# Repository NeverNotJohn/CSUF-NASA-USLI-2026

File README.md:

# California State University, Fresno NASA USLI 
California State University, Fresno (CSUF) GitHub for the 2025-2026 NASA USLI Competition 

## File Structure
### Hardware
Schematics, PCB, KiCad project, etc.
### Software
Code made in C/C++ using FreeRTOS and Arduino. Development using the PlatformIO IDE

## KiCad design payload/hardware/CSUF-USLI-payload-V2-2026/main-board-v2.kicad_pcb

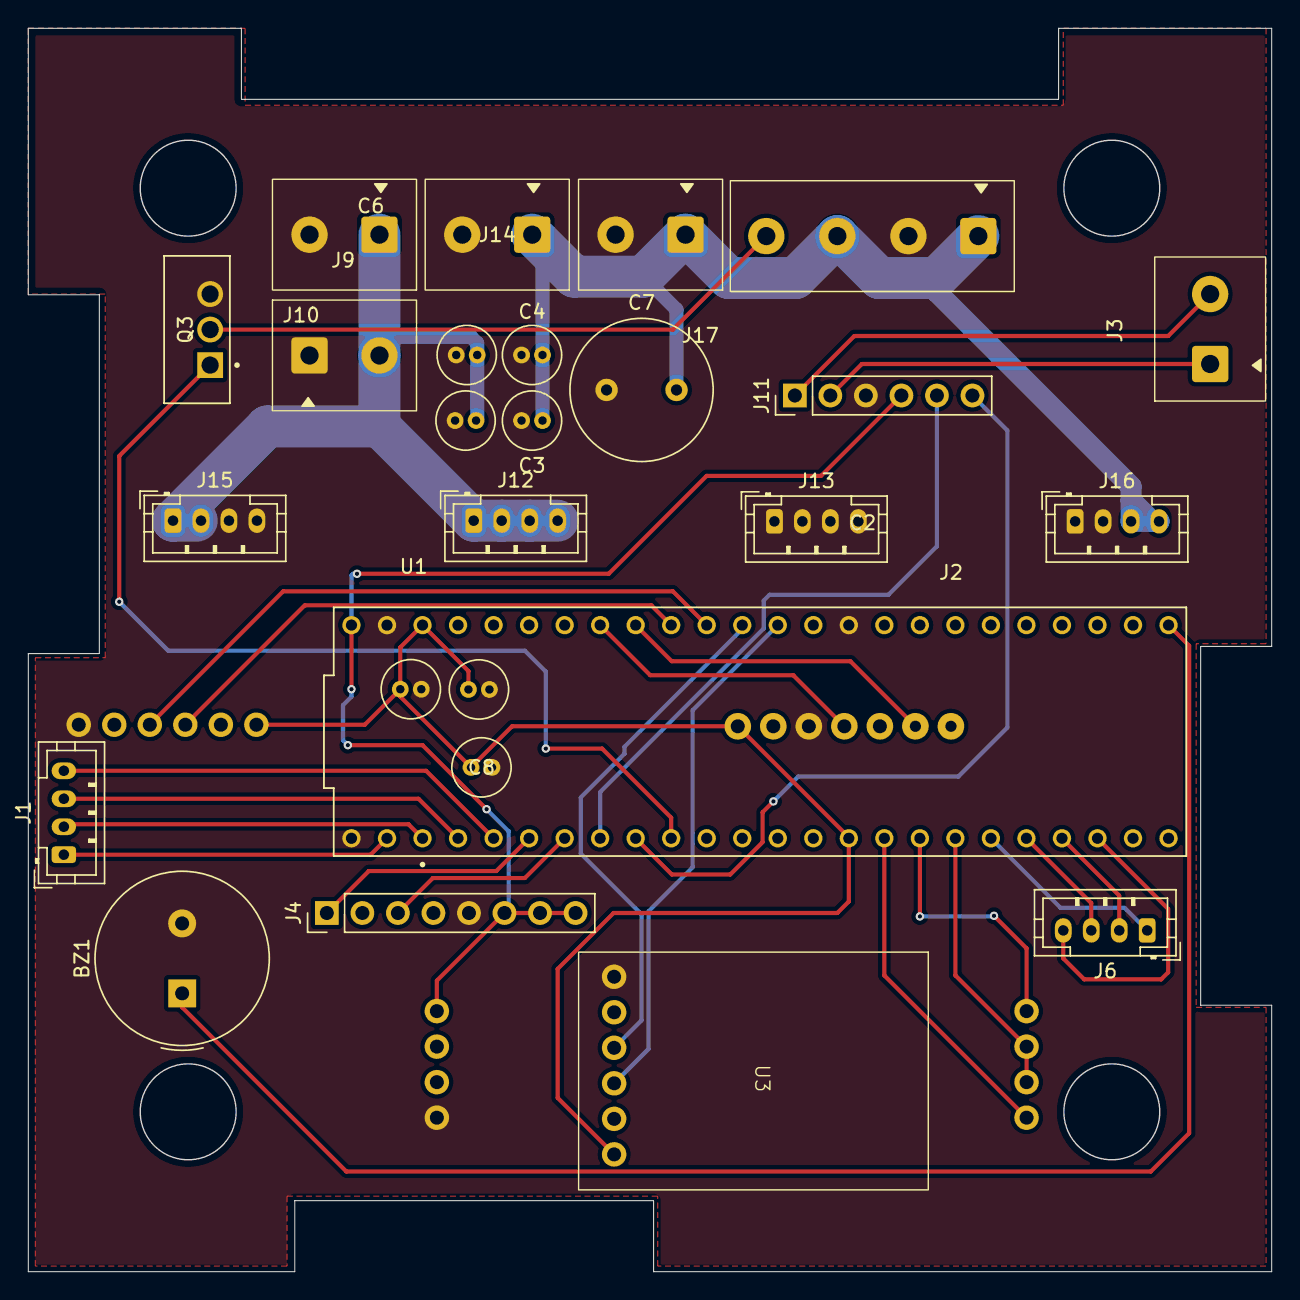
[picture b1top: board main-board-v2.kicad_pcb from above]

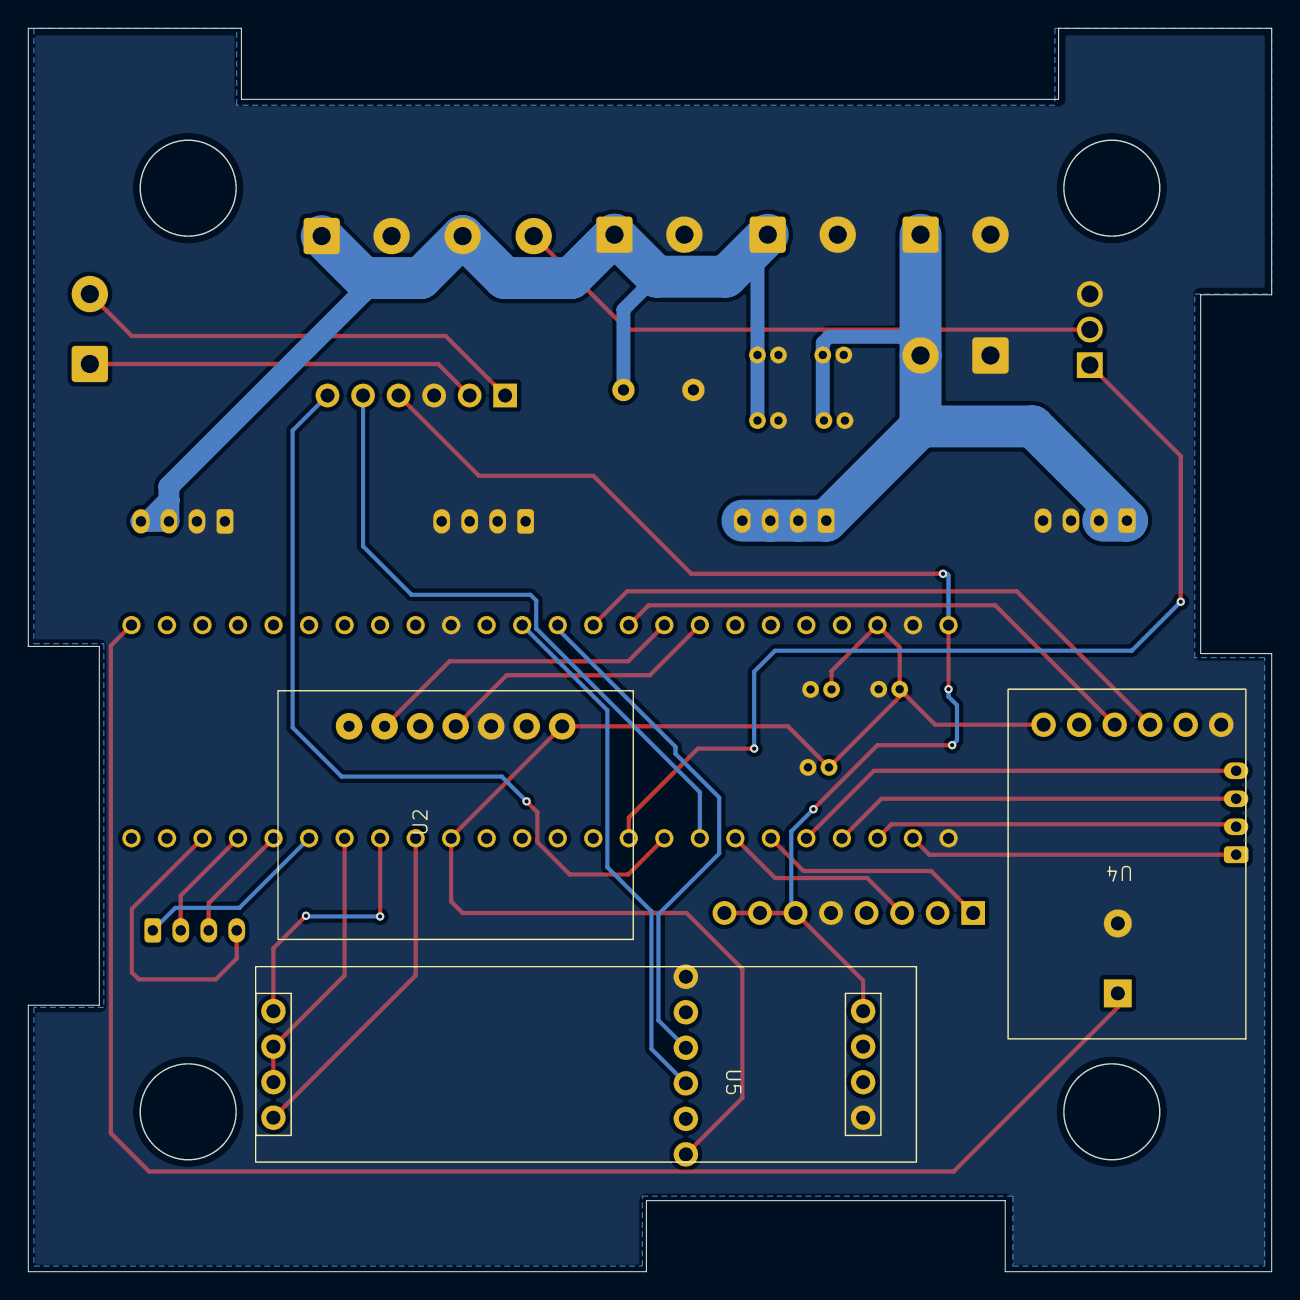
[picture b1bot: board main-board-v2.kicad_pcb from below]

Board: 2 copper layers, 88.9 x 88.9 mm, 29 parts (3 on the bottom side), 31 nets.

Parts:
BZ1: Buzzer; Buzzer_TDK_PS1240P02BT_D12.2mm_H6.5mm
C1, C2, C3, C5, C8: 0.1 uF; C_Radial_D4.0mm_H7.0mm_P1.50mm
C4, C6: 1 uF; C_Radial_D4.0mm_H7.0mm_P1.50mm
C7: 330 uF; C_Radial_D10.0mm_H12.5mm_P5.00mm
J1: Servo JST; JST_PH_B4B-PH-K_1x04_P2.00mm_Vertical
J2: Drill x 11.1V OUT; Edit_TerminalBlock_Phoenix_MKDS-1,5-2_1x04_P5.00mm_Horizont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
J3: Motor Power; Edit_TerminalBlock_Phoenix_MKDS-1,5-2_1x02_P5.00mm_Horizont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
J4: BTS7960 Output; PinHeader_1x08_P2.54mm_Vertical
J6: Reserve JST; JST_PH_B4B-PH-K_1x04_P2.00mm_Vertical
J9: Soil Sensor Power; Edit_TerminalBlock_Phoenix_MKDS-1,5-2_1x02_P5.00mm_Horizont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
J10: 8.4V IN; Edit_TerminalBlock_Phoenix_MKDS-1,5-2_1x02_P5.00mm_Horizont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
J11: Chassis Input; PinHeader_1x06_P2.54mm_Vertical
J12: Servo VCC; JST_PH_B4B-PH-K_1x04_P2.00mm_Vertical
J13: Servo GND; JST_PH_B4B-PH-K_1x04_P2.00mm_Vertical
J14: 11.1V IN; Edit_TerminalBlock_Phoenix_MKDS-1,5-2_1x02_P5.00mm_Horizont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
J15: 8.4V RESERVE; JST_PH_B4B-PH-K_1x04_P2.00mm_Vertical
J16: 11.1V RESERVE; JST_PH_B4B-PH-K_1x04_P2.00mm_Vertical
J17: Driver Input; Edit_TerminalBlock_Phoenix_MKDS-1,5-2_1x02_P5.00mm_Horizont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
Q3: IRLZ44N
U1: DEV-16771; MODULE_DEV-16771
U2: Adafruit BMP280; BMP280
U3, U4: RYLR896; REYAX RYLR896
U5: Modbus to UART; Modbus_to_UART

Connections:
+3V3: C1.1, C2.1, C8.1, U1.3.3V_1 (3.3V), U1.3.3V_2 (3.3V), U2.1 (Vin), U3.1 (VDD), U4.1 (VDD)
+5V: J4.6, J4.7, J4.8, J11.4, U1.VIN, U5.5 (VCC)
+8.4V: C5.2, C6.2, J9.2, J10.1, J12.1, J12.2, J12.3, J12.4, J15.1, J15.2
+11.1V: C3.2, C4.2, C7.2, J2.1, J2.3, J14.1, J16.3, J16.4, J17.1
Chassis_Encoder_A: J11.5, U1.6 (OUT1D)
Chassis_Encoder_B: J11.6, U1.7 (RX2)
DRILL: Q3.1 (G), U1.8 (TX2)
GND: BZ1.2 (-), C1.2, C2.2, C3.1, C4.1, C5.1, C6.1, C7.1, C8.2, J2.2, J4.5, J9.1, J10.2, J11.3, J13.1, J13.2, J13.3, J13.4, J14.2, J15.3, J15.4, J16.1, J16.2, J17.2, Q3.3 (S), U1.GND1 (GND), U1.GND2 (GND), U1.GND3 (GND), U2.3 (GND), U3.6 (GND), U4.6 (GND), U5.8 (GND)
LPWM: J4.3, U1.5 (IN2)
unnamed: BZ1.1 (+), U1.33 (MCLK2)
unnamed: J2.4, Q3.2 (D)
unnamed: J3.2, J11.1
unnamed: J3.1, J11.2
RESERVE_0: J6.1, U1.27 (A13)
RESERVE_1: J6.2, U1.29 (TX7)
RESERVE_2: J6.3, U1.28 (RX7)
RESERVE_3: J6.4, U1.30 (CRX3)
RPWM: J4.1, U1.4 (BCLK2)
RX3: U1.15 (A1), U3.4 (TXD)
RX4: U1.16 (A2), U4.4 (TXD)
RX6: U1.25 (A11), U5.4 (RO)
SCL: U1.19 (A5), U2.4 (SCK)
SDA: U1.18 (A4), U2.6 (SDI)
SERVO_0: J1.1, U1.0 (RX1)
SERVO_1: J1.2, U1.1 (TX1)
SERVO_2: J1.3, U1.2 (OUT2)
SERVO_3: J1.4, U1.3 (LRCLK2)
SOIL_ENABLE: U1.26 (A12), U5.2 (DE), U5.3 (RE)
TX3: U1.14 (A0), U3.3 (RXD)
TX4: U1.17 (A3), U4.3 (RXD)
TX6: U1.24 (A10), U5.1 (DI)

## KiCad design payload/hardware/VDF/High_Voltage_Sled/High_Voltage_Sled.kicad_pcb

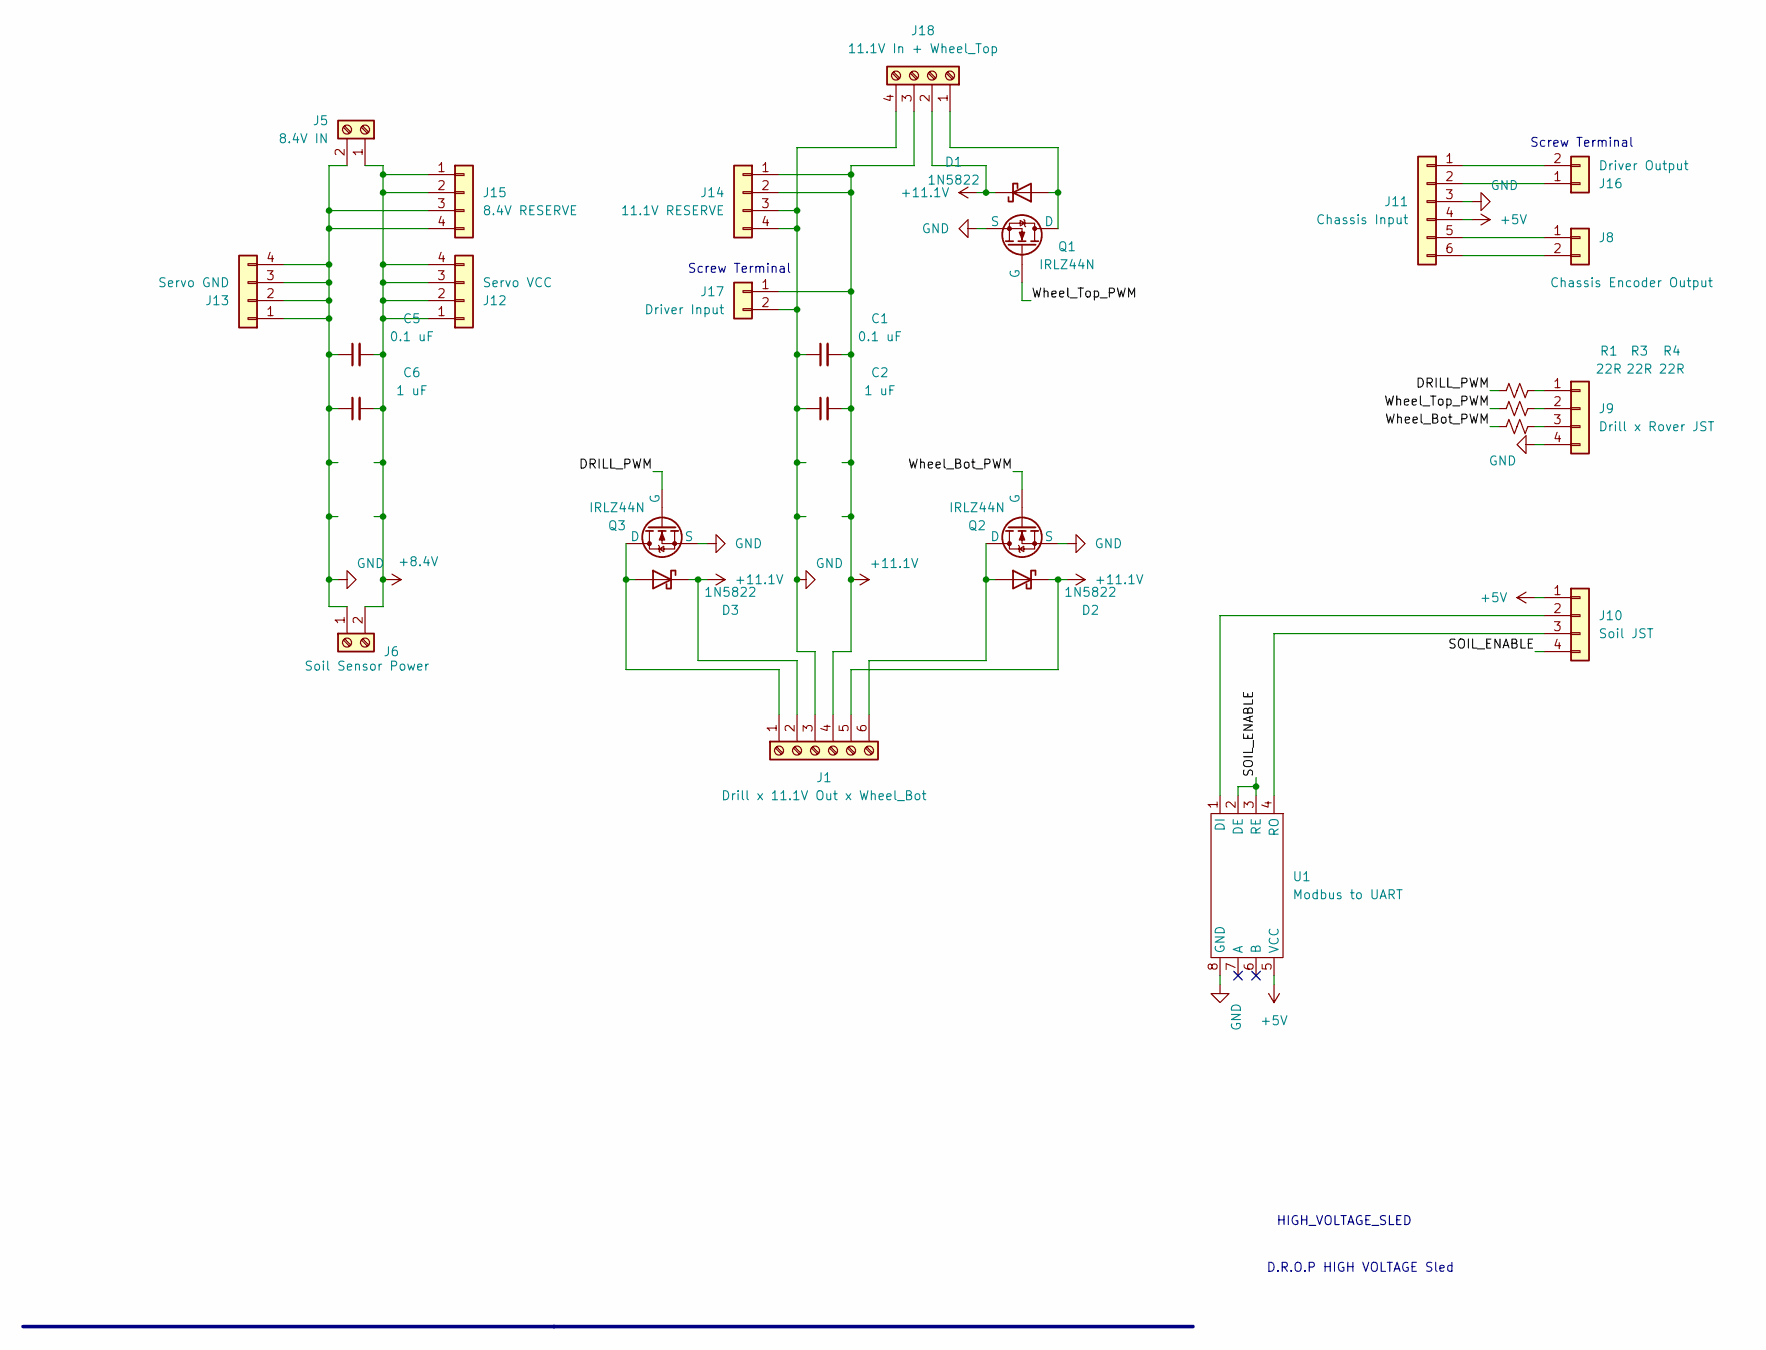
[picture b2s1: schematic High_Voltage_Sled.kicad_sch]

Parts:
C1, C5: 0.1 uF; C_Radial_D4.0mm_H7.0mm_P1.50mm
C2, C6: 1 uF; C_Radial_D4.0mm_H7.0mm_P1.50mm
D1, D2, D3: 1N5822; D_DO-201AD_P15.24mm_Horizontal
J1: Drill x 11.1V Out x Wheel_Bot; Edit_TerminalBlock_Phoenix_MKDS-1,5-2_1x06_P5.00mm_Horizont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
J5: 8.4V IN; Edit_TerminalBlock_Phoenix_MKDS-1,5-2_1x02_P5.00mm_Horizont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
J6: Soil Sensor Power; Edit_TerminalBlock_Phoenix_MKDS-1,5-2_1x02_P5.00mm_Horizont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
J8: Chassis Encoder Output; JST_PH_B2B-PH-K_1x02_P2.00mm_Vertical
J9: Drill x Rover JST; JST_PH_B4B-PH-K_1x04_P2.00mm_Vertical
J10: Soil JST; JST_PH_B4B-PH-K_1x04_P2.00mm_Vertical
J11: Chassis Input; PinHeader_1x06_P2.54mm_Vertical
J12: Servo VCC; JST_PH_B4B-PH-K_1x04_P2.00mm_Vertical
J13: Servo GND; JST_PH_B4B-PH-K_1x04_P2.00mm_Vertical
J14: 11.1V RESERVE; JST_PH_B4B-PH-K_1x04_P2.00mm_Vertical
J15: 8.4V RESERVE; JST_PH_B4B-PH-K_1x04_P2.00mm_Vertical
J16: Driver Output; Edit_TerminalBlock_Phoenix_MKDS-1,5-2_1x02_P5.00mm_Horizont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
J17: Driver Input; Edit_TerminalBlock_Phoenix_MKDS-1,5-2_1x02_P5.00mm_Horizont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
J18: 11.1V In + Wheel_Top; Edit_TerminalBlock_Phoenix_MKDS-1,5-2_1x04_P5.00mm_Horizont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
Q1, Q2, Q3: IRLZ44N
R1, R3, R4: 22R; R_Axial_DIN0207_L6.3mm_D2.5mm_P2.54mm_Vertical
U1: Modbus to UART; Modbus_to_UART

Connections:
+5V: J10.1, J11.4, U1.5 (VCC)
+8.4V: C5.2, C6.2, J5.1, J6.2, J12.1, J12.2, J12.3, J12.4, J15.1, J15.2
+11.1V: C1.2, C2.2, D1.1 (K), D2.1 (K), D3.1 (K), J1.2, J1.4, J1.5, J14.1, J14.2, J17.1, J18.2, J18.3
/DRILL_PWM: Q3.1 (G), R4.1
/SOIL_ENABLE: J10.4, U1.2 (DE), U1.3 (RE)
/Wheel_Bot_PWM: Q2.1 (G), R3.1
/Wheel_Top_PWM: Q1.1 (G), R1.1
GND: C1.1, C2.1, C5.1, C6.1, J1.3, J5.2, J6.1, J9.4, J11.3, J13.1, J13.2, J13.3, J13.4, J14.3, J14.4, J15.3, J15.4, J17.2, J18.4, Q1.3 (S), Q2.3 (S), Q3.3 (S), U1.8 (GND)
unnamed: D1.2 (A), J18.1, Q1.2 (D)
unnamed: D2.2 (A), J1.6, Q2.2 (D)
unnamed: D3.2 (A), J1.1, Q3.2 (D)
unnamed: J9.1, R4.2
unnamed: J9.2, R1.2
unnamed: J9.3, R3.2
unnamed: J10.2, U1.1 (DI)
unnamed: J10.3, U1.4 (RO)
unnamed: J11.1, J16.2
unnamed: J11.2, J16.1
unnamed: J8.1, J11.5
unnamed: J8.2, J11.6

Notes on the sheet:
Screw Terminal
HIGH_VOLTAGE_SLED
D.R.O.P HIGH VOLTAGE Sled

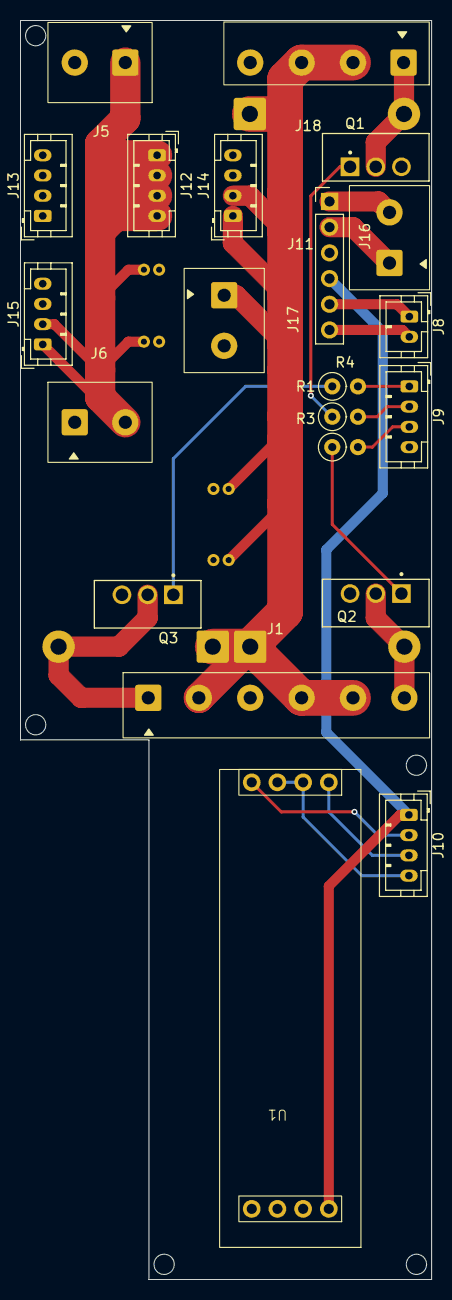
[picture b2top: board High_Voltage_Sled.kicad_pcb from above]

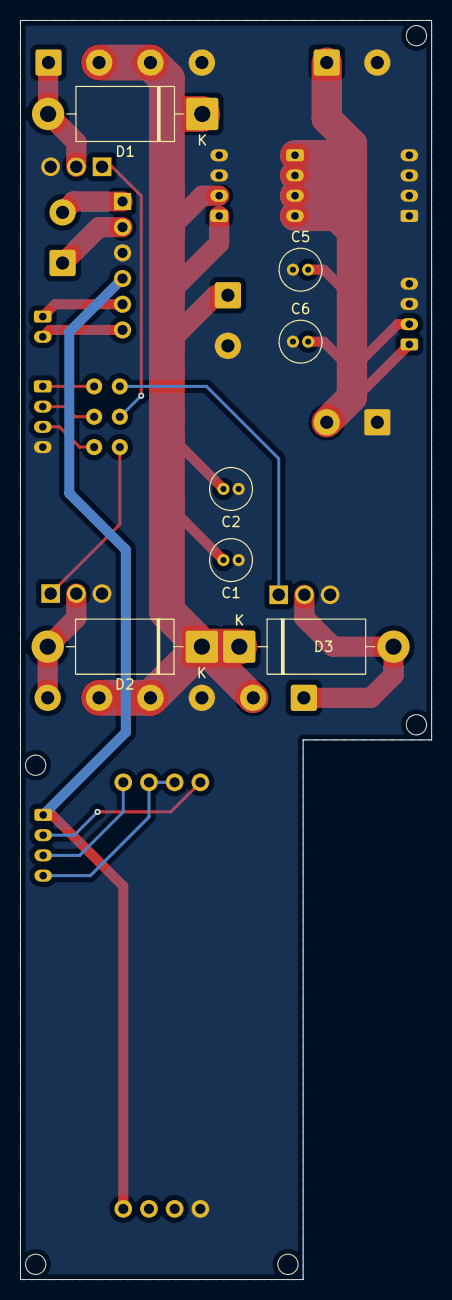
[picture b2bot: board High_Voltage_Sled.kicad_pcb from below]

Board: 2 copper layers, 40.6 x 124.5 mm, 28 parts (7 on the bottom side), 20 nets.

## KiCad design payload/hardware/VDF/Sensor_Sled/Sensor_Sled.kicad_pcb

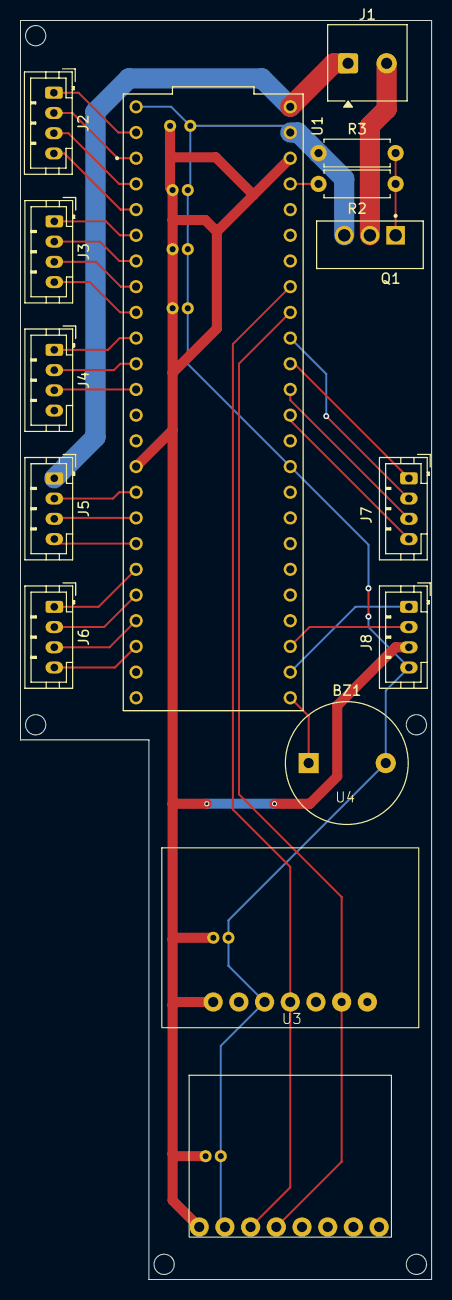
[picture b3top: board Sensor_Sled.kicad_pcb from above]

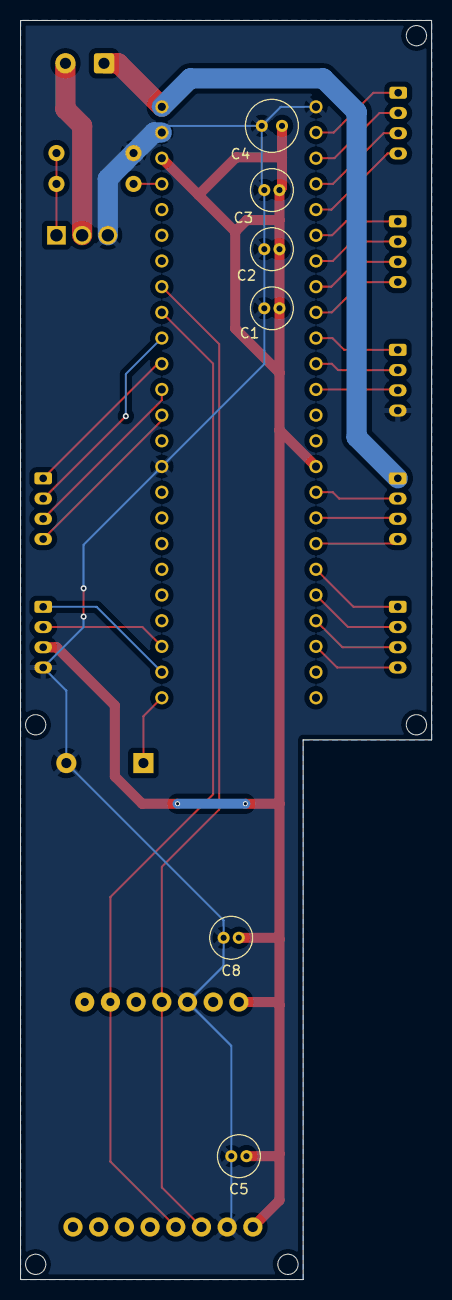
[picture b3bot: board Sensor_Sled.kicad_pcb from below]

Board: 2 copper layers, 40.6 x 124.5 mm, 21 parts (6 on the bottom side), 33 nets.

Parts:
BZ1: Buzzer; Buzzer_TDK_PS1240P02BT_D12.2mm_H6.5mm
C1, C5, C8: 0.1 uF; C_Radial_D4.0mm_H7.0mm_P1.50mm
C2: 1 uF; C_Radial_D4.0mm_H7.0mm_P1.50mm
C3: 10 uF; C_Radial_D4.0mm_H7.0mm_P1.50mm
C4: 100 uF; C_Radial_D5.0mm_H7.0mm_P2.00mm
J1: TD3 Connection; TerminalBlock_Phoenix_MKDS-1-2-3.81_1x02_P3.81mm_Horizontal
J2: Servo JST; JST_PH_B4B-PH-K_1x04_P2.00mm_Vertical
J3: Chassis JST; JST_PH_B4B-PH-K_1x04_P2.00mm_Vertical
J4: Drill x Rover JST; JST_PH_B4B-PH-K_1x04_P2.00mm_Vertical
J5: Soil JST; JST_PH_B4B-PH-K_1x04_P2.00mm_Vertical
J6: Reserve JST; JST_PH_B4B-PH-K_1x04_P2.00mm_Vertical
J7: RYLR896 JST; JST_PH_B4B-PH-K_1x04_P2.00mm_Vertical
J8: GPS x Power JST; JST_PH_B4B-PH-K_1x04_P2.00mm_Vertical
Q1: IRLZ44N
R2: 330; R_Axial_DIN0207_L6.3mm_D2.5mm_P7.62mm_Horizontal
R3: 10k; R_Axial_DIN0207_L6.3mm_D2.5mm_P7.62mm_Horizontal
U1: DEV-16771; MODULE_DEV-16771
U3: MPU6050
U4: Adafruit BMP280; BMP280

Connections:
+3V3: C1.1, C2.1, C3.1, C4.1, C5.1, C8.1, J8.3, U1.3.3V_1 (3.3V), U1.3.3V_2 (3.3V), U3.1 (VCC), U4.1 (Vin)
+5V: J1.1, J5.1, U1.VIN
/Chassis_Encoder_A: J3.3, U1.6 (OUT1D)
/Chassis_Encoder_B: J3.4, U1.7 (RX2)
/Chassis_Out_0: J3.1, U1.4 (BCLK2)
/Chassis_Out_1: J3.2, U1.5 (IN2)
/DRILL: J4.1, U1.8 (TX2)
/RESERVE_0: J6.1, U1.27 (A13)
/RESERVE_1: J6.2, U1.28 (RX7)
/RESERVE_2: J6.3, U1.29 (TX7)
/RESERVE_3: J6.4, U1.30 (CRX3)
/ROVER_BOT: J4.3, U1.10 (CS1)
/ROVER_TOP: J4.2, U1.9 (OUT1C)
/RX3: J7.3, U1.15 (A1)
/RX4: J7.1, U1.16 (A2)
/RX6: J5.3, U1.25 (A11)
/RX8: J8.1, U1.34 (RX8)
/SERVO_0: J2.1, U1.0 (RX1)
/SERVO_1: J2.2, U1.1 (TX1)
/SERVO_2: J2.3, U1.2 (OUT2)
/SERVO_3: J2.4, U1.3 (LRCLK2)
/SOIL_ENABLE: J5.4, U1.26 (A12)
/TX3: J7.4, U1.14 (A0)
/TX4: J7.2, U1.17 (A3)
/TX6: J5.2, U1.24 (A10)
/TX8: J8.2, U1.35 (TX8)
GND: BZ1.2 (-), C1.2, C2.2, C3.2, C4.2, C5.2, C8.2, J4.4, J8.4, Q1.3 (S), R3.1, U1.GND1 (GND), U1.GND2 (GND), U1.GND3 (GND), U3.2 (GND), U4.3 (GND)
unnamed: BZ1.1 (+), U1.33 (MCLK2)
unnamed: J1.2, Q1.2 (D)
unnamed: Q1.1 (G), R2.2, R3.2
unnamed: U1.18 (A4), U3.4 (SDA), U4.6 (SDI)
unnamed: U1.19 (A5), U3.3 (SCL), U4.4 (SCK)
unnamed: R2.1, U1.23 (A9)

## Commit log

2025-09-25 Creating Readme
2025-09-25 Created PlatformIO project
2025-09-25 Creating Tempalte for Code - This is BEFORE FreeRTOS
2025-09-26 Made changes to FreeRTOS
2025-09-26 Added KiCad
2025-09-30 some changes
2025-09-30 changed main naming scheme
2025-10-01 Made updates to the file structure
2025-10-03 updated file structure
2025-10-14 changed git ignore to ignore KiCad stuff
2025-10-14 changed naming convention
2025-10-14 Merging Init PCB changes
2025-10-15 made some changes
2025-10-15 asdAdded changes n stuff
2025-10-16 ejfioahsfaspkaspdk
2025-10-17 Motor Diagram Concept
2025-10-18 Added decoupling capacitors
2025-10-20 added BMP280
2025-10-20 BMP280 and LoRa RYLR896 symbols
2025-10-20 Added the final soil sensors
2025-10-27 idk what change i did
2025-10-27 Added ground station schematic
2025-10-29 Rover Subsystem
    Created "generic" symbol library to hold generic symbols (including the 12v drill created earlier)
2025-11-01 Revert "Merge pull request #4 from NeverNotJohn/PDR_Schematic"
    This reverts commit b304c00c3a6b217adf7fd74d4069b9ba7e955c17, reversing
    changes made to a2006b1930044f0c3205c7475f893156ef9e6752.
2025-11-02 KiCad does not like merge requests
2025-11-07 BMP280 Library
    Added in getters for pressure, temp, relative altitude. Also created a calibrating function.
2025-11-07 Changed to doubles
    "double calculateBaselinePressure()"
    "dobule getPressure()"
2025-11-07 MPU6050 Init Library
    connects via I2C on pins 17+18 at address 0x68 or 0x69 (AD0 pin pulled high).
2025-11-07 Don't merge this
    can compile because of issues with defines header file
2025-11-07 Read gyro and accel
    Implementation of "getAcceleration()" and "getAngularAcceleration"
    Vector3D struct is defined in the "MPU6050.h" header file
2025-11-09 Calculate orientation
    "getAngularAcceleration()" to "getAngularVelocity()" (I am an idiot)
    proof of concept "orientationLoop()"
    Drifts very fast, prints to the serial monitor in degrees not very accurate.
2025-11-09 complementary filter
    updated "orientationCalculation()".
    - mutates a vec3 in place.
    - complementary filter with accelerometer data
2025-11-09 unused libs
2025-11-09 BMP280 Library (#5)
    * BMP280 Library
    Added in getters for pressure, temp, relative altitude. Also created a calibrating function.
    * Changed to doubles
    "double calculateBaselinePressure()"
    "dobule getPressure()"
    * Update bmp280.h
2025-11-09 MPU6050 Init Library (#6)
    * MPU6050 Init Library
    connects via I2C on pins 17+18 at address 0x68 or 0x69 (AD0 pin pulled high).
    * Don't merge this
    can compile because of issues with defines header file
    * Read gyro and accel
    Implementation of "getAcceleration()" and "getAngularAcceleration"
2025-11-09 Fixed function output types
2025-11-09 MadgwickAHRS
    Usage of a Madgwick filter for orientation
2025-11-09 merge conflicts
    insane amount of merge conflicts
2025-11-09 output type
2025-11-09 semaphore mutex, madgwick
    can read both the mpu6050 and bmp280 at the "same " time.
    also implements the Madgwick filter for the mpu6050
2025-11-13 First Draft of Schematic
2025-11-14 Refactored main to do my bidding
2025-11-14 Created beep task for funzies
2025-11-14 Create RYLR cpp and header
2025-11-14 Added comments
2025-11-14 Added Some comments
2025-11-14 Added ANNOY_CYAN Flag
2025-11-14 Fixed Some Spacing
2025-11-14 RYLR896 Won't accept inputs
2025-11-14 Time is working now i think lol
2025-11-14 im in pain
2025-11-14 init commit
2025-11-19 wow thats a lot of storage
2025-11-19 hmm changing my idea
2025-11-19 cleaned up lib and preparing for FreeRTOS stuff
2025-11-19 Created I2C header and yeeted to others
2025-11-19 Created I2C header and yeeted to others (#8)
2025-11-19 cleaned code up and increased bmp accuracy
2025-11-20 NEO6M Intergration
    added
    functions to init and get values using the tinygpsplus library
2025-11-25 changed serial port
2025-11-25 Fixed Mutex Glitches
2025-11-25 Bmp280 library (#9)
    * BMP280 Library
    Added in getters for pressure, temp, relative altitude. Also created a calibrating function.
    * Changed to doubles
    "double calculateBaselinePressure()"
    "dobule getPressure()"
    * Update bmp280.h
2025-11-25 cleanup n stuff
2025-11-25 Made changes to debug
2025-11-25 Usage of semaphore and a mutex to read sensors without conflict. Implementation of Madgwick filter. (#7)
    * semaphore mutex, madgwick
    can read both the mpu6050 and bmp280 at the "same " time.
    also implements the Madgwick filter for the mpu6050
    * Update main.cpp
    * Refactored main to do my bidding
    * s
2025-11-26 Created Main task and added buzzer mutex
2025-12-01 changed flight counters
2025-12-02 yay it works
2025-12-02 Single Squashed commit
2025-12-02 MOved time cause i fcked up the merge
2025-12-04 yata
2025-12-05 changed LED output pin
2025-12-07 ignore main.cpp
2025-12-07 SD Card (#12)
    * ignore main.cpp
    * init commit
2025-12-07 Main task (#13)
    * semaphore mutex, madgwick
    can read both the mpu6050 and bmp280 at the "same " time.
    also implements the Madgwick filter for the mpu6050
    * Update main.cpp
    * NEO6M Intergration
    added
2025-12-07 Fixed Pull Request
2025-12-07 Added Mutex for coolio stuff
2025-12-07 Rylr896 (#14)
    * Create RYLR cpp and header
    * Added comments
    * Added Some comments
    * Added ANNOY_CYAN Flag
    * Fixed Some Spacing
    * RYLR896 Won't accept inputs
2025-12-08 mysterious bug has arisen!
2025-12-23 finished base logger
2025-12-23 Logger (#15)
    * mysterious bug has arisen!
    * finished base logger
2025-12-26 i dont even wanna begin to explain
2025-12-26 ground station receives yay
2025-12-26 finished ground station integration
2025-12-26 finished ground station
2025-12-26 Ground comms (#16)
    * i dont even wanna begin to explain
    * ground station receives yay
    * finished ground station integration
    * finished ground station
2025-12-27 subscale ready!
2025-12-27 sd card init
2025-12-27 Fixed SD card now Subscale Ready!!!
2025-12-30 init drill motor
2025-12-30 implementation
    can drive motor forwards + backwards and stop it.
2026-01-06 CDR Schematic done
2026-01-31 soil sensor yay
2026-01-31 Drill Motor Driver (#17)
    * init drill motor
    * implementation
    can drive motor forwards + backwards and stop it.
    ---------
2026-01-31 soil sensor yay (#18)
2026-02-24 init
    servo control class,
    tweaking lowk
2026-02-27 add mission state
2026-02-27 mission state real
2026-02-27 Revert "init"
    This reverts commit 94947be4726dddcf734dfc7228caaad16aa90498.
2026-02-27 im so confused
2026-02-27 Revert "init"
2026-02-27 servocontrol files
2026-02-27 mission state 1
2026-02-27 inital flippy code
2026-02-28 legs part 2
2026-02-28 update ground station
2026-02-28 bro this is cooked
2026-02-28 checking
2026-03-08 Current VDF
2026-03-14 MPU 6050 w filter
2026-03-16 mission state servo libs
2026-03-16 Sensor Sled Done Pls Check connections
2026-03-24 Fix mission state
2026-03-24 fixed up
2026-03-25 printed stuff
2026-03-25 Implement PCB Soil Sensor
    Implemented the soil sensor onto the PCB. Constantly prints, packet is not done yet.
2026-03-25 Vdf pcb (#21)
    * Sensor Sled Done Pls Check connections
    * printed stuff
2026-03-27 yay soil stuff
2026-03-27 yay soil stuff (#22)
2026-03-28 Testing commands and first post-flight algos
2026-03-28 ahhhhhhhhhhhhhhh
2026-03-30 Servo speed changes, toggles
2026-04-01 New PCB
    Changed into one board, not all parts are placed, the screw holes are not in the right place as they were based on the measurements of a smaller 3.1inch plate not the 3.5 inch plate. Clearance for le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
2026-04-01 Updated dimensions
    Updated the position of the screw holes and slot. Made the corners rounded to match ig idk.
2026-04-02 placing componenets
    bruh
2026-04-04 init
2026-04-04 init chassis stuff
2026-04-05 go full scale go
2026-04-05 change drill pin
2026-04-07 fix ground station CSV writing
2026-04-07 trying to route traces
    bad bad bad
2026-04-09 pcb reroute
    traces are doomed 0 errors on DRC!
2026-04-24 fix drill pin, fix chassis stuff, fix soil, test commands
    sheesh
2026-04-29 67676767676676
